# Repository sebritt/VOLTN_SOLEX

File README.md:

# VOLTN_SOLEX
This is the official repo of VOLT'N SOLEX

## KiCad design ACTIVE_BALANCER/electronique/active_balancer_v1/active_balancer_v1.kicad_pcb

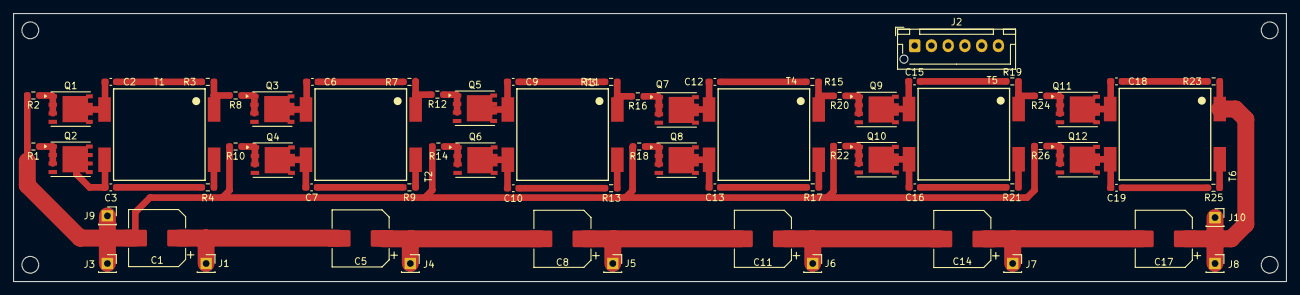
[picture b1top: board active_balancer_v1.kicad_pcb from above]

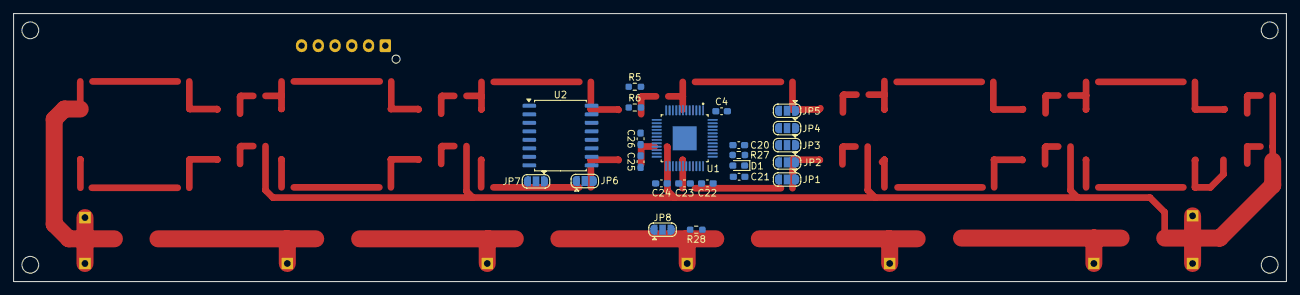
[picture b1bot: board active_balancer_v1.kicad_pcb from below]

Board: 2 copper layers, 189.9 x 40.0 mm, 93 parts (23 on the bottom side), 86 nets.

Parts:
C1, C5, C8, C11, C14, C17: 60uF 10V; CP_Elec_8x10
C2, C3, C6, C7, C9, C10, C12, C13, C15, C16, C18, C19: 100pF 100V; C_0603_1608Metric_Pad1.08x0.95mm_HandSolder
C4: 10uF 10V; C_0603_1608Metric_Pad1.08x0.95mm_HandSolder
C20, C21, C22, C23, C24, C25, C26: 0.1uF 10V; C_0603_1608Metric_Pad1.08x0.95mm_HandSolder
D1: D_Schottky; D_0603_1608Metric_Pad1.05x0.95mm_HandSolder
J1, J3, J4, J5, J6, J7, J8, J9, J10: Conn_01x01_Socket; PinSocket_1x01_P2.54mm_Vertical
J2: JST_XH_6pin_SPI; JST_XH_B6B-XH-AM_1x06_P2.50mm_Vertical
JP1: JUMPER_A1; SolderJumper-3_P1.3mm_Open_RoundedPad1.0x1.5mm
JP2: JUMPER_A2; SolderJumper-3_P1.3mm_Open_RoundedPad1.0x1.5mm
JP3: JUMPER_A3; SolderJumper-3_P1.3mm_Open_RoundedPad1.0x1.5mm
JP4: JUMPER_A4; SolderJumper-3_P1.3mm_Open_RoundedPad1.0x1.5mm
JP5: JUMPER_A5; SolderJumper-3_P1.3mm_Open_RoundedPad1.0x1.5mm
JP6: JUMPER_EN_NUM_ISO_IN; SolderJumper-3_P1.3mm_Open_RoundedPad1.0x1.5mm
JP7: JUMPER_EN_NUM_ISO_OUT; SolderJumper-3_P1.3mm_Open_RoundedPad1.0x1.5mm
JP8: Whatchdog Timer; SolderJumper-3_P1.3mm_Open_RoundedPad1.0x1.5mm
Q1, Q2, Q3, Q4, Q5, Q6, Q7, Q8, Q9, Q10, Q11, Q12: SIR882DP 100V 60A; SIR882DP_PowerPAK_SO-8_Single
R1, R2, R8, R10, R12, R14, R16, R18, R20, R22, R24, R26: 10m; R_0603_1608Metric_Pad0.98x0.95mm_HandSolder
R3, R4, R7, R9, R11, R13, R15, R17, R19, R21, R23, R25: 330; R_0603_1608Metric_Pad0.98x0.95mm_HandSolder
R5: 23.33k; R_0603_1608Metric_Pad0.98x0.95mm_HandSolder
R6: 7.5k; R_0603_1608Metric_Pad0.98x0.95mm_HandSolder
R27: 6.5; R_0603_1608Metric_Pad0.98x0.95mm_HandSolder
R28: 2.5k; R_0603_1608Metric_Pad0.98x0.95mm_HandSolder
T1, T2, T3, T4, T5, T6: 750312504 1:2 ISAT=10A 3.5uF; WE-FLYLT_EP13_2381
U1: LTC3300ILXE-2_PBF; QFP50P900X900X160-49N
U2: ADuM1401xRW; SOIC-16W_7.5x10.3mm_P1.27mm

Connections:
5V: J2.6, JP7.1 (A), U2.1 (VDD1)
/CELL_1+: C1.1, C5.2, C25.2, C26.1, J1.1, R3.1, R8.2, T1.1 (AA), U1.24 (C1)
/CELL_1-: C1.2, C4.2, C26.2, J3.1, J9.1, JP1.1 (A), JP2.1 (A), JP3.1 (A), JP4.1 (A), JP5.1 (A), JP6.3 (B), JP8.1 (A), R1.2, R2.2, R5.2, R6.2, R10.2, R14.2, R18.2, R22.2, R26.2, U1.15 (CTRL), U1.21 (V-), U1.49 (V-), U2.9 (GND2), U2.15 (GND2)
/CELL_2+: C5.1, C8.2, C24.2, C25.1, J4.1, R7.1, R12.2, T2.1 (AA), U1.27 (C2)
/CELL_3+: C8.1, C11.2, C23.2, C24.1, J5.1, R11.1, R16.2, T3.1 (AA), U1.30 (C3)
/CELL_4+: C11.1, C14.2, C22.2, C23.1, J6.1, R15.1, R20.2, T4.1 (AA), U1.33 (C4)
/CELL_5+: C14.1, C17.2, C21.2, C22.1, J7.1, R19.1, R24.2, T5.1 (AA), U1.36 (C5)
/CELL_6+: C17.1, C21.1, D1.2 (A), J8.1, J10.1, R23.1, T6.1 (AA), U1.39 (C6)
/LT3300_A0: JP1.2 (C), U1.43 (A0)
/LT3300_A1: JP2.2 (C), U1.44 (A1)
/LT3300_A2: JP3.2 (C), U1.45 (A2)
/LT3300_A3: JP4.2 (C), U1.46 (A3)
/LT3300_A4: JP5.2 (C), U1.47 (A4)
/LT3300_BOOST: C4.1, JP1.3 (B), JP2.3 (B), JP3.3 (B), JP4.3 (B), JP5.3 (B), JP6.1 (A), R28.1, U1.42 (BOOST), U1.48 (VREG), U2.16 (VDD2)
/LT3300_BOOSTN: C20.2, U1.41 (BOOSTN)
/LT3300_BOOSTP: C20.1, R27.1, U1.40 (BOOSTP)
/LT3300_CSBI: U1.16 (~CSBI), U2.14 (VOA)
/LT3300_G1P: Q1.2 (G), U1.23 (G1P)
/LT3300_G1S: Q2.2 (G), U1.11 (G1S)
/LT3300_G2P: Q3.2 (G), U1.26 (G2P)
/LT3300_G2S: Q4.2 (G), U1.9 (G2S)
/LT3300_G3P: Q5.2 (G), U1.29 (G3P)
/LT3300_G3S: Q6.2 (G), U1.7 (G3S)
/LT3300_G4P: Q7.2 (G), U1.32 (G4P)
/LT3300_G4S: Q8.2 (G), U1.5 (G4S)
/LT3300_G5P: Q9.2 (G), U1.35 (G5P)
/LT3300_G5S: Q10.2 (G), U1.3 (G5S)
/LT3300_G6P: Q11.2 (G), U1.38 (G6P)
/LT3300_G6S: Q12.2 (G), U1.1 (G6S)
/LT3300_I1P: Q1.3 (S), R2.1, U1.22 (I1P)
/LT3300_I1S: Q2.3 (S), R1.1, U1.12 (I1S)
/LT3300_I2P: Q3.3 (S), R8.1, U1.25 (I2P)
/LT3300_I2S: Q4.3 (S), R10.1, U1.10 (I2S)
/LT3300_I3P: Q5.3 (S), R12.1, U1.28 (I3P)
/LT3300_I3S: Q6.3 (S), R14.1, U1.8 (I3S)
/LT3300_I4P: Q7.3 (S), R16.1, U1.31 (I4P)
/LT3300_I4S: Q8.3 (S), R18.1, U1.6 (I4S)
/LT3300_I5P: Q9.3 (S), R20.1, U1.34 (I5P)
/LT3300_I5S: Q10.3 (S), R22.1, U1.4 (I5S)
/LT3300_I6P: Q11.3 (S), R24.1, U1.37 (I6P)
/LT3300_I6S: Q12.3 (S), R26.1, U1.2 (I6S)
/LT3300_RTONP: R5.1, U1.14 (RTONP)
/LT3300_RTONS: R6.1, U1.13 (RTONS)
/LT3300_SCKI: U1.17 (SCKI), U2.13 (VOB)
/LT3300_SDI: U1.18 (SDI), U2.12 (VOC)
/LT3300_SDO: U1.19 (SDO), U2.11 (VID)
/LT3300_WDT: JP8.2 (C), U1.20 (WDT)
GLOBAL_LT3300_CS: J2.5, U2.3 (VIA)
GLOBAL_LT3300_SCK: J2.4, U2.4 (VIB)
GLOBAL_LT3300_SDI: J2.3, U2.5 (VIC)
GLOBAL_LT3300_SDO: J2.2, U2.6 (VOD)
GND: J2.1, JP7.3 (B), U2.2 (GND1), U2.8 (GND1)
unnamed: C2.1, R3.2
unnamed: C3.1, R4.2
unnamed: C6.1, R7.2
unnamed: C7.1, R9.2
unnamed: C9.1, R11.2
unnamed: C10.1, R13.2
unnamed: C12.1, R15.2
unnamed: C13.1, R17.2
unnamed: C15.1, R19.2
unnamed: C16.1, R21.2
unnamed: C18.1, R23.2
unnamed: C19.1, R25.2
unnamed: D1.1 (K), R27.2
unnamed: JP6.2 (C), U2.10 (VE2)
unnamed: JP7.2 (C), U2.7 (VE1)
unnamed: JP8.3 (B), R28.2
unnamed: C2.2, Q1.1 (D), T1.2 (AB)
unnamed: C3.2, Q2.1 (D), T1.3 (SA)
unnamed: C6.2, Q3.1 (D), T2.2 (AB)
unnamed: C7.2, Q4.1 (D), T2.3 (SA)
unnamed: C9.2, Q5.1 (D), T3.2 (AB)
unnamed: C10.2, Q6.1 (D), T3.3 (SA)
unnamed: C12.2, Q7.1 (D), T4.2 (AB)
unnamed: C13.2, Q8.1 (D), T4.3 (SA)
unnamed: C15.2, Q9.1 (D), T5.2 (AB)
unnamed: C16.2, Q10.1 (D), T5.3 (SA)
unnamed: C18.2, Q11.1 (D), T6.2 (AB)
unnamed: C19.2, Q12.1 (D), T6.3 (SA)
unnamed: R4.1, T1.4 (SB)
unnamed: R9.1, T2.4 (SB)
unnamed: R13.1, T3.4 (SB)
unnamed: R17.1, T4.4 (SB)
unnamed: R21.1, T5.4 (SB)
unnamed: R25.1, T6.4 (SB)

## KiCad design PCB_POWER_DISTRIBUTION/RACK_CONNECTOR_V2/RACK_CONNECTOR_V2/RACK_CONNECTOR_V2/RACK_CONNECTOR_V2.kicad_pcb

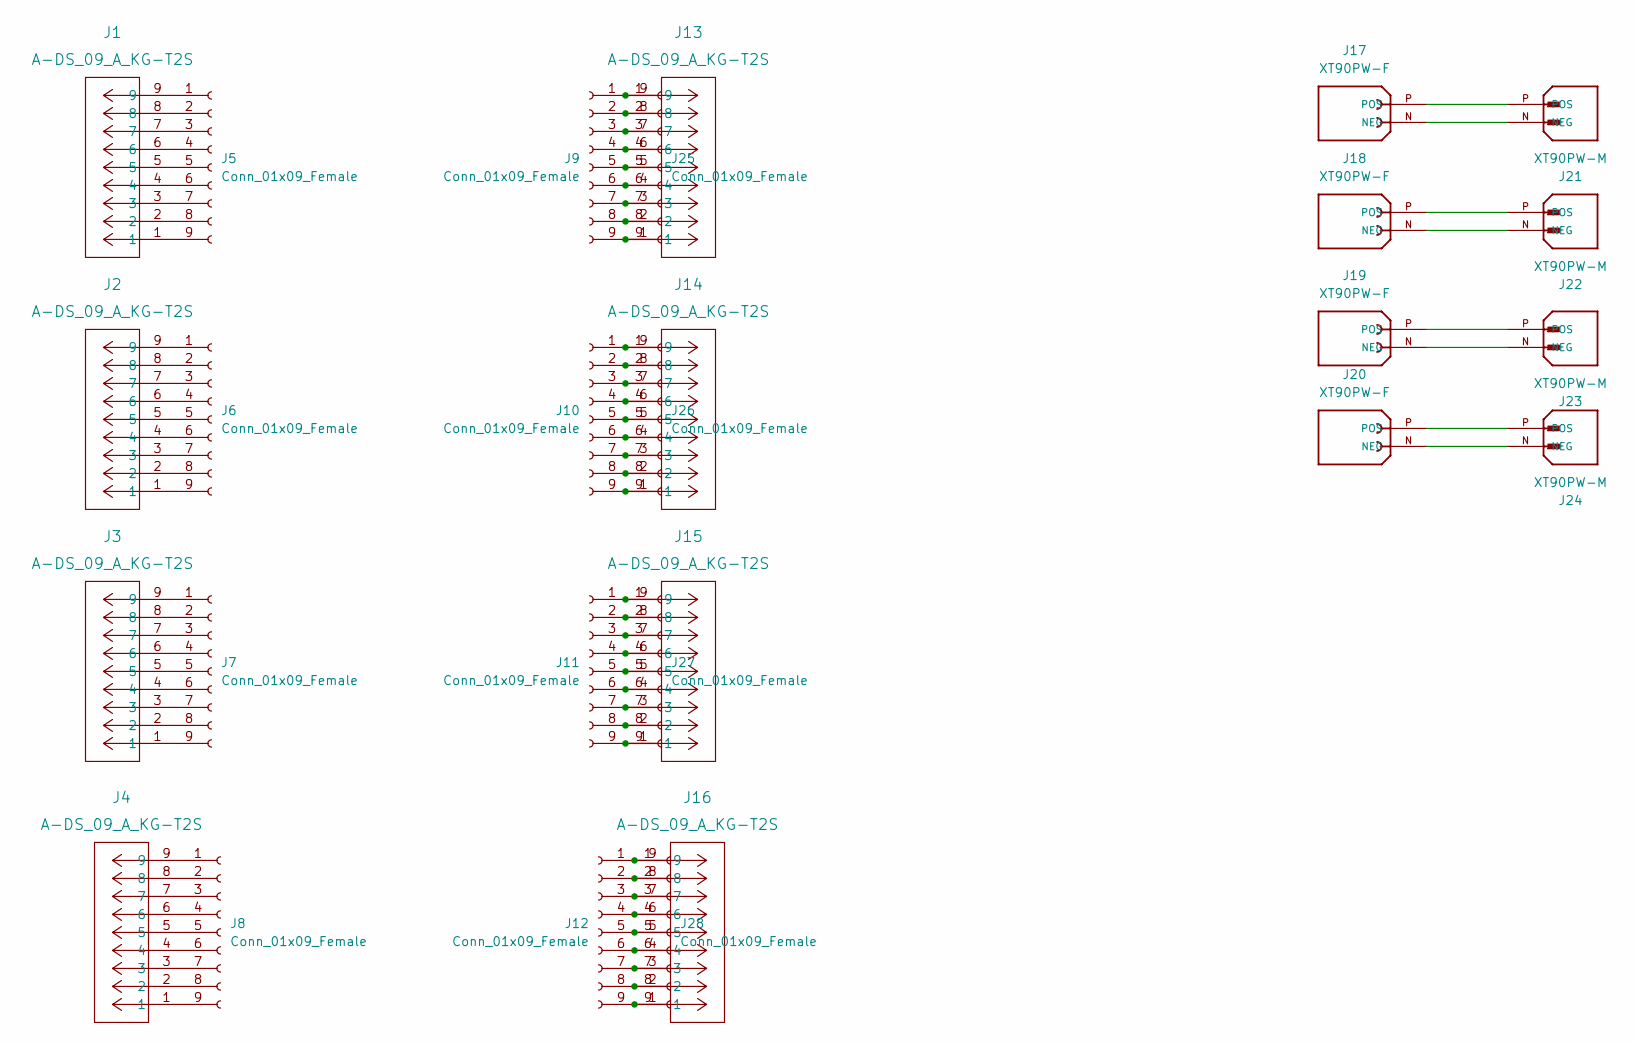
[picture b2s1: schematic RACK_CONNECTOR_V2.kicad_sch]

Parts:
J1, J2, J3, J4, J13, J14, J15, J16: A-DS_09_A_KG-T2S; ASSMANN_A-DF_09_A_KG-T2S
J5, J6, J7, J8, J9, J10, J11, J12, J25, J26, J27, J28: Conn_01x09_Female; PinHeader_1x09_P2.54mm_Vertical
J17, J18, J19, J20: XT90PW-F; AMASS_XT90PW-F; PARTREV V00
J21, J22, J23, J24: XT90PW-M; AMASS_XT90PW-M; PARTREV V00

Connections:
unnamed: J1.1, J5.9
unnamed: J1.2, J5.8
unnamed: J1.3, J5.7
unnamed: J1.4, J5.6
unnamed: J1.5, J5.5
unnamed: J1.6, J5.4
unnamed: J1.7, J5.3
unnamed: J1.8, J5.2
unnamed: J1.9, J5.1
unnamed: J2.1, J6.9
unnamed: J2.2, J6.8
unnamed: J2.3, J6.7
unnamed: J2.4, J6.6
unnamed: J2.5, J6.5
unnamed: J2.6, J6.4
unnamed: J2.7, J6.3
unnamed: J2.8, J6.2
unnamed: J2.9, J6.1
unnamed: J3.1, J7.9
unnamed: J3.2, J7.8
unnamed: J3.3, J7.7
unnamed: J3.4, J7.6
unnamed: J3.5, J7.5
unnamed: J3.6, J7.4
unnamed: J3.7, J7.3
unnamed: J3.8, J7.2
unnamed: J3.9, J7.1
unnamed: J4.1, J8.9
unnamed: J4.2, J8.8
unnamed: J4.3, J8.7
unnamed: J4.4, J8.6
unnamed: J4.5, J8.5
unnamed: J4.6, J8.4
unnamed: J4.7, J8.3
unnamed: J4.8, J8.2
unnamed: J4.9, J8.1
unnamed: J10.1, J14.9, J26.1
unnamed: J10.2, J14.8, J26.2
unnamed: J10.3, J14.7, J26.3
unnamed: J10.4, J14.6, J26.4
unnamed: J10.5, J14.5, J26.5
unnamed: J10.6, J14.4, J26.6
unnamed: J10.7, J14.3, J26.7
unnamed: J10.8, J14.2, J26.8
unnamed: J10.9, J14.1, J26.9
unnamed: J11.1, J15.9, J27.1
unnamed: J11.2, J15.8, J27.2
unnamed: J11.3, J15.7, J27.3
unnamed: J11.4, J15.6, J27.4
unnamed: J11.5, J15.5, J27.5
unnamed: J11.6, J15.4, J27.6
unnamed: J11.7, J15.3, J27.7
unnamed: J11.8, J15.2, J27.8
unnamed: J11.9, J15.1, J27.9
unnamed: J12.1, J16.9, J28.1
unnamed: J12.2, J16.8, J28.2
unnamed: J12.3, J16.7, J28.3
unnamed: J12.4, J16.6, J28.4
unnamed: J12.5, J16.5, J28.5
unnamed: J12.6, J16.4, J28.6
unnamed: J12.7, J16.3, J28.7
unnamed: J12.8, J16.2, J28.8
unnamed: J12.9, J16.1, J28.9
unnamed: J9.9, J13.1, J25.9
unnamed: J9.8, J13.2, J25.8
unnamed: J9.7, J13.3, J25.7
unnamed: J9.6, J13.4, J25.6
unnamed: J9.5, J13.5, J25.5
unnamed: J9.4, J13.6, J25.4
unnamed: J9.3, J13.7, J25.3
unnamed: J9.2, J13.8, J25.2
unnamed: J9.1, J13.9, J25.1
unnamed: J17.N (NEG), J21.N (NEG)
unnamed: J17.P (POS), J21.P (POS)
unnamed: J18.N (NEG), J22.N (NEG)
unnamed: J18.P (POS), J22.P (POS)
unnamed: J19.N (NEG), J23.N (NEG)
unnamed: J19.P (POS), J23.P (POS)
unnamed: J20.N (NEG), J24.N (NEG)
unnamed: J20.P (POS), J24.P (POS)

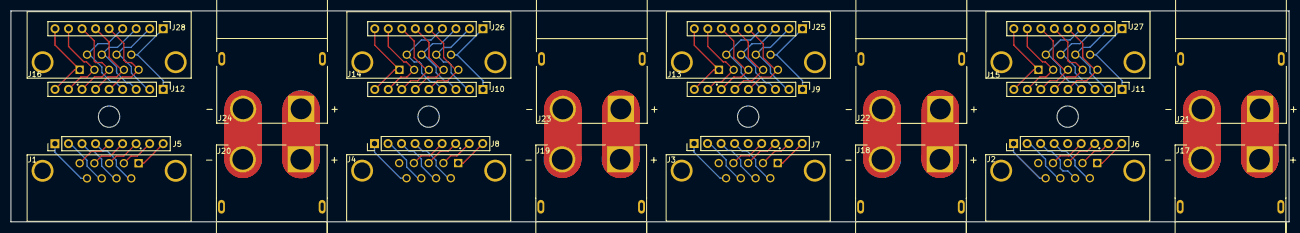
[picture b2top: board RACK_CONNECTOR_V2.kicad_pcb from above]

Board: 2 copper layers, 240.0 x 39.6 mm, 28 parts (0 on the bottom side), 80 nets.

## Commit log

2024-02-29 added all the loacal files
2024-02-29 added the display part
2024-02-29 Update V1_affichage_sans_VESC.ino
    Template affichage sur LCD 16*2
2024-02-29 Added descriptions files
2024-02-29 updated with bare minimum for screen setup
2024-02-29 Added the old code from 2023 and updated the bare minimum code
2024-02-29 added the basics functions to update the LCD value
2024-02-29 added comment
2024-02-29 removed error from LCD_printInt() function
2024-03-02 V2 PCB save no rooting done
2024-03-03 all the footprint and rooting is done
2024-03-03 added the busbar
2024-03-03 added more busbar and placing name of the part on the silkscreen
2024-03-03 added the holes for fixation
2024-03-03 Update affichage valeurs ESC
    - creation d'une structure Data contenant les valeurs à affichées
    A faire :
    connexion ADC pour récupérer batteryTemp
2024-04-09 version fonctionnel, mais avec un pb sur LCD_printInt
2024-11-20 started the active balancer circuit
2024-11-21 finished the schematic need a review to make shure everything is okay and after pcb placing & routing while be made. Note this active balancer is for 6s scallable easly for 64s
2024-11-21 Updated the pcb rooting and created a step file to check the finting in fusion 360
2025-05-26 update of the last modification
2025-05-26 Moved all the old file into the old folder for a fresh start
2025-05-26 Added the SOLEX_LOGGER
2025-05-26 suppress all the old unescessary file
2025-05-26 added instal dependencies scirpts
2025-05-26 Added the TODOLIST.mkd
2025-05-26 Added the TODOLIST
2025-06-07 New structure : one script for csv & serie
2025-06-07 move old version
2025-06-08 add terminal
2025-06-08 add box movements
2025-06-08 button to move boxes
2025-06-08 update de code
2025-06-08 SOLEX_LOG_V3 fonctionne mais sans LoRa
2025-06-10 updated code, + LOG0000_VESC.csv
2025-06-10 serie mod
2025-06-10 one page, rm index.html
2025-06-10 ajout data esc, gyro max, bouton clear (v1 il est moche)
2025-06-12 refresh btn v2/ vMax filter
2025-06-12 add pictures
2025-06-13 bite
